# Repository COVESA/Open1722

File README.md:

<!-- PROJECT LOGO -->
<br />
<div align="center">

<h2 align="center">COVESA Open1722</h2>

  <p align="center">
    Open1722  is an implementation of the IEEE 1722 protocol, for streaming audio/video, tunneling CAN/LIN messages and enabling remote access to peripheral bus systems.
    <br />
    <br />
    <a href="https://github.com/COVESA/Open1722/issues">Report Bug</a>
    ·
    <a href="https://github.com/COVESA/Open1722/issues">Request Feature</a>
    </p>
</div>

### Maintainers

* [Naresh Nayak - University of Applied Sciences Furtwangen (HFU)](https://github.com/nayakned)
* [Adriaan Niess - Robert Bosch GmbH](https://github.com/adriaan-niess)
* [Sebastian Schildt - University of Applied Sciences Heilbronn (HHN)](https://github.com/SebastianSchildt)

## Introduction

Open1722 is a fork of [AVNU/libavtp](https://github.com/Avnu/libavtp) which is an open source reference implementation of the Audio Video Transport Protocol (AVTP) specified in IEEE 1722-2025 spec. _libavtp_ primarily focuses on audio video data formats of the IEEE 1722-2016 spec.

IEEE 1722 is also gaining a lot of traction in the automotive community, mainly, to bridge fieldbus technologies over automotive Ethernet. In particular the AVTP Control Formats (ACF) specify serialization for a set of data formats relevant for automotive applications (e.g., CAN, LIN, etc.). Open1722 extends/modifies _libavtp_ to also include these ACF formats.

Open1722 is under BSD License. For more information see LICENSE file.

## Implementation

This repository is organized as follows:
- The `src/` and `include/` folders contain the IEEE 1722 protocol implementation. We strive to make the implementation platform independant and avoid usage of platform specific headers or libraries. For now the implementation is tested only on Linux.
- The `examples/` folder contains various applications that use our Open1722 library. Most applications are targeted to Linux platforms. Few applications (e.g. [_acf-can-bridge_](./examples/acf-can/zephyr/)) are also ported for Zephyr RTOS. Compilation instructions for Zephyr is available in the corresponding folder of the application.

Before building Open1722 make sure you have installed the following software :
* CMake >= 3.20
* CMocka >= 1.1.0 (For running unit tests. This can be installed on Debian/Ubuntu using ```sudo apt install libcmocka-dev```)

Alternatively, you can use VS Code to run the provided dev container which takes care of the dependencies.

The first step to build Open1722 is to generate the Makefile and build the project.
```
$ mkdir build
$ cd build
$ cmake ..
$ make
```
This builds the libraries _libopen1722_ containing all the data formats specified in the IEEE 1722-2025 specification along with _libopen1722custom_ which contains customized serialization formats which can be sent over IEEE 1722.

To execute available unit tests:
```
$ cmake ..
$ make unittests
$ make test
```

The [examples](./examples/) can be built as follows:
```
$ make examples
```

The build can be cleaned using the following command:
```
$ make clean
```

To install Open1722 on your system run:
```
$ sudo make install
```

To cross-compile for aarch64 (e.g. Raspberry Pi), you can use the [toolchain file](./aarch64.toolchain) we provided. Note that this requires a fresh build process with a new ```build``` folder.
```
$ sudo apt install gcc-aarch64-linux-gnu libc6-dev-arm64-cross binutils-aarch64-linux-gnu
$ cmake .. -DCMAKE_TOOLCHAIN_FILE=../aarch64.toolchain
$ make
```

## AVTP Formats Support

AVTP protocol defines several AVTPDU type formats (see Table 7 from IEEE 1722-2025 spec).

The following is the list of the formats currently supported by Open1722:
 - AAF (PCM encapsulation only)
 - CRF
 - CVF (H.264, MJPEG, JPEG2000)
 - RVF
 - AVTP Control Formats (ACF) with Non-Time-Synchronous as well as Time-Synchronous formats (see Table 23 from IEEE 1722-2025 spec)
    - CAN (v1 & v2)
    - CAN Brief (v1 & v2)
    - CAN-XL
    - CAN-XL Brief
    - CRC
    - Flexray
    - LIN
    - MOST
    - GPC
    - Sensor
    - Sensor Brief
    - Generic Byte Bus
    - Abbreviated Byte Bus
    - Generic Image Sensor Format (GISF)
    - I2C
    - I2C Brief
  - Custom formats not included in the standard but can be transported on top of IEEE 1722
    - COVESA Vehicle Signal Specification (VSS) [(Protocol description)](./examples/acf-vss/protocol_description/acf-vss.md)

## Examples

The `examples/` directory provides sample applications which demonstrate the Open1722 functionalities. Each example directory contains a README file that includes specific details on its functionality, configuration, and dependencies.

To execute the IEEE 1722 CAN Talker application:
```
$ ./build/examples/acf-can/linux/acf-can-talker
```

### Programming Tutorial

Here's a small example how the Open1722 library can be used to build and parse IEEE 1722 Protocol Data Units (aka PDUs). First define a C struct for a custom IEEE 1722 packet that can be used to transport a CAN and a LIN message. The frame begins with a Time-synchronous Control Format (TSCF) header. Alternatively a Non-Timesynchronous Control Format (NTSCF) header could be used. After the TSCF header a list of AVTP Control Format (ACF) messages follows. The first ACF message is a ACF CAN message which consists of ACF CAN header as well as a payload section to carry an 8-byte CAN frame. Similarly to the CAN message, another ACF message for LIN is added.

When combining IEEE 1722 header/message structs directly in memory to form a packet, the resulting layout must not contain compiler-inserted padding bytes. Use a compiler hint to enforce packed layout (for example `__attribute__((packed))` with GCC/Clang).

``` C
// my_1722_pdu.h

#include "avtp/Udp.h"
#include "avtp/acf/Tscf.h"
#include "avtp/acf/Can.h"
#include "avtp/acf/Lin.h"

#define CAN_PAYLOAD_LEN 8
#define LIN_PAYLOAD_LEN 4

typedef struct __attribute__((packed)) {
    // IEEE 1722 UDP encapsulation header (optional)
    Avtp_Udp_t udp;
    // IEEE 1722 TSCF header (version 0 layout; use Avtp_TscfV1_t for version 1)
    Avtp_TscfV0_t tscf;
    // IEEE 1722 ACF message #1
    Avtp_Can_t can;
    uint8_t canPayload[CAN_PAYLOAD_LEN];
    // IEEE 1722 ACF message #2
    Avtp_Lin_t lin;
    uint8_t linPayload[LIN_PAYLOAD_LEN];
} My1722Pdu_t;
```

In the next step we're going to c

``` C
// talker.h

#include "my_1722_pdu.h"

int main()
{
    My1722Pdu_t pdu;

    // Init UDP encapsulation header
    Avtp_Udp_Init(&pdu.udp);

    // Init TSCF header. Use Avtp_Tscf_Init(&pdu.tscf, version) to pick the
    // version at runtime; version 0 and version 1 have different layouts and
    // header lengths (Avtp_TscfV0_t / Avtp_TscfV1_t).
    Avtp_Tscf_InitV0(&pdu.tscf);
    Avtp_CommonHeader_SetVersion((Avtp_CommonHeader_t *)&pdu.tscf, 0);
    Avtp_Tscf_SetSequenceNum(&pdu.tscf, 123);
    Avtp_Tscf_SetStreamId(&pdu.tscf, 0xAABBCCDDEEFF);
    Avtp_Tscf_SetTv(&pdu.tscf, true);
    Avtp_Tscf_SetAvtpTimestamp(&pdu.tscf, 0x11223344);

    // Init CAN ACF message
    Avtp_Can_Init(&pdu.can);
    Avtp_Can_SetCanBusId(&pdu.can, 4);
    uint8_t canFrame[CAN_PAYLOAD_LEN] = {0x11, 0x22, 0x33, 0x44, 0x55, 0x66, 0x77, 0x88};
    memcpy(pdu.can.payload, canFrame, CAN_PAYLOAD_LEN);

    // Init LIN ACF message
    Avtp_Lin_Init(&pdu.lin);
    uint8_t linFrame[LIN_PAYLOAD_LEN] = {0x11, 0x22, 0x33, 0x44};
    memcpy(pdu.lin.payload, linFrame, LIN_PAYLOAD_LEN);

    // Send packet to network using socket API ...
    uint8_t* data = &pdu;
    size_t dataLen = sizeof(My1722Pdu_t);
    // int socket = ...
    // sendto(socket, data, dataLen, 0);
}
```

## Open1722 API

To learn what you can expect from the Open1722 API and to get a starting point in case you want to extend Open1722 see the [API design documentation](docs/api-design.md).

## Alignment and Performance

PDUs may sit at any byte offset in a buffer: the accessors make no alignment assumptions, and on targets with hardware unaligned access the field-access engine still compiles to single-instruction reads and writes. See [alignment.md](docs/alignment.md) for the spec background, the generated-code details, and how to hint a guaranteed alignment on strict-alignment targets.

## Inline Functions and Shared Library Exports

Open1722 uses `static inline` functions for field accessors to enable compiler optimizations on embedded targets. These same functions are also exported as regular symbols in the shared library for FFI users. See [inline.md](docs/inline.md) for details.

## Rust
Open1722 is consciously implemented in C and designed to effciently run on anything with a processor. Now we _do_ know Rust is awesome and has many advantages for some use cases. If you happen to be one of those guys: There is probably no need to wrap Open1722 yourself or endavour in yet another "let's rewrite it in Rust" initiative. Instead, check out this nice third-party wrapper to Open1722 first: https://crates.io/crates/open1722/

## Contribute to Open1722

For detailed information see our [contribution guide](./CONTRIBUTING.md)!

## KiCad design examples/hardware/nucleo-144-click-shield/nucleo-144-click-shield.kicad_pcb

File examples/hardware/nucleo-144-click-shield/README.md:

# NUCLEO-144 Click Shield

This directory contains the KiCad project for the NUCLEO-144 Click Shield, a hardware add-on board designed to attach mikroBus click boards to an STM32 NUCLEO-144 development board. This clicks shield is useful to run various Open1722 examples for Zephyr on a modular platform.

## Use

Open the `.kicad_pro` file in KiCad to work with the project. From there you can edit the schematic, update the PCB layout, and regenerate fabrication outputs.

If you need a stable reference for the released design, use the files in `v1.1/`.

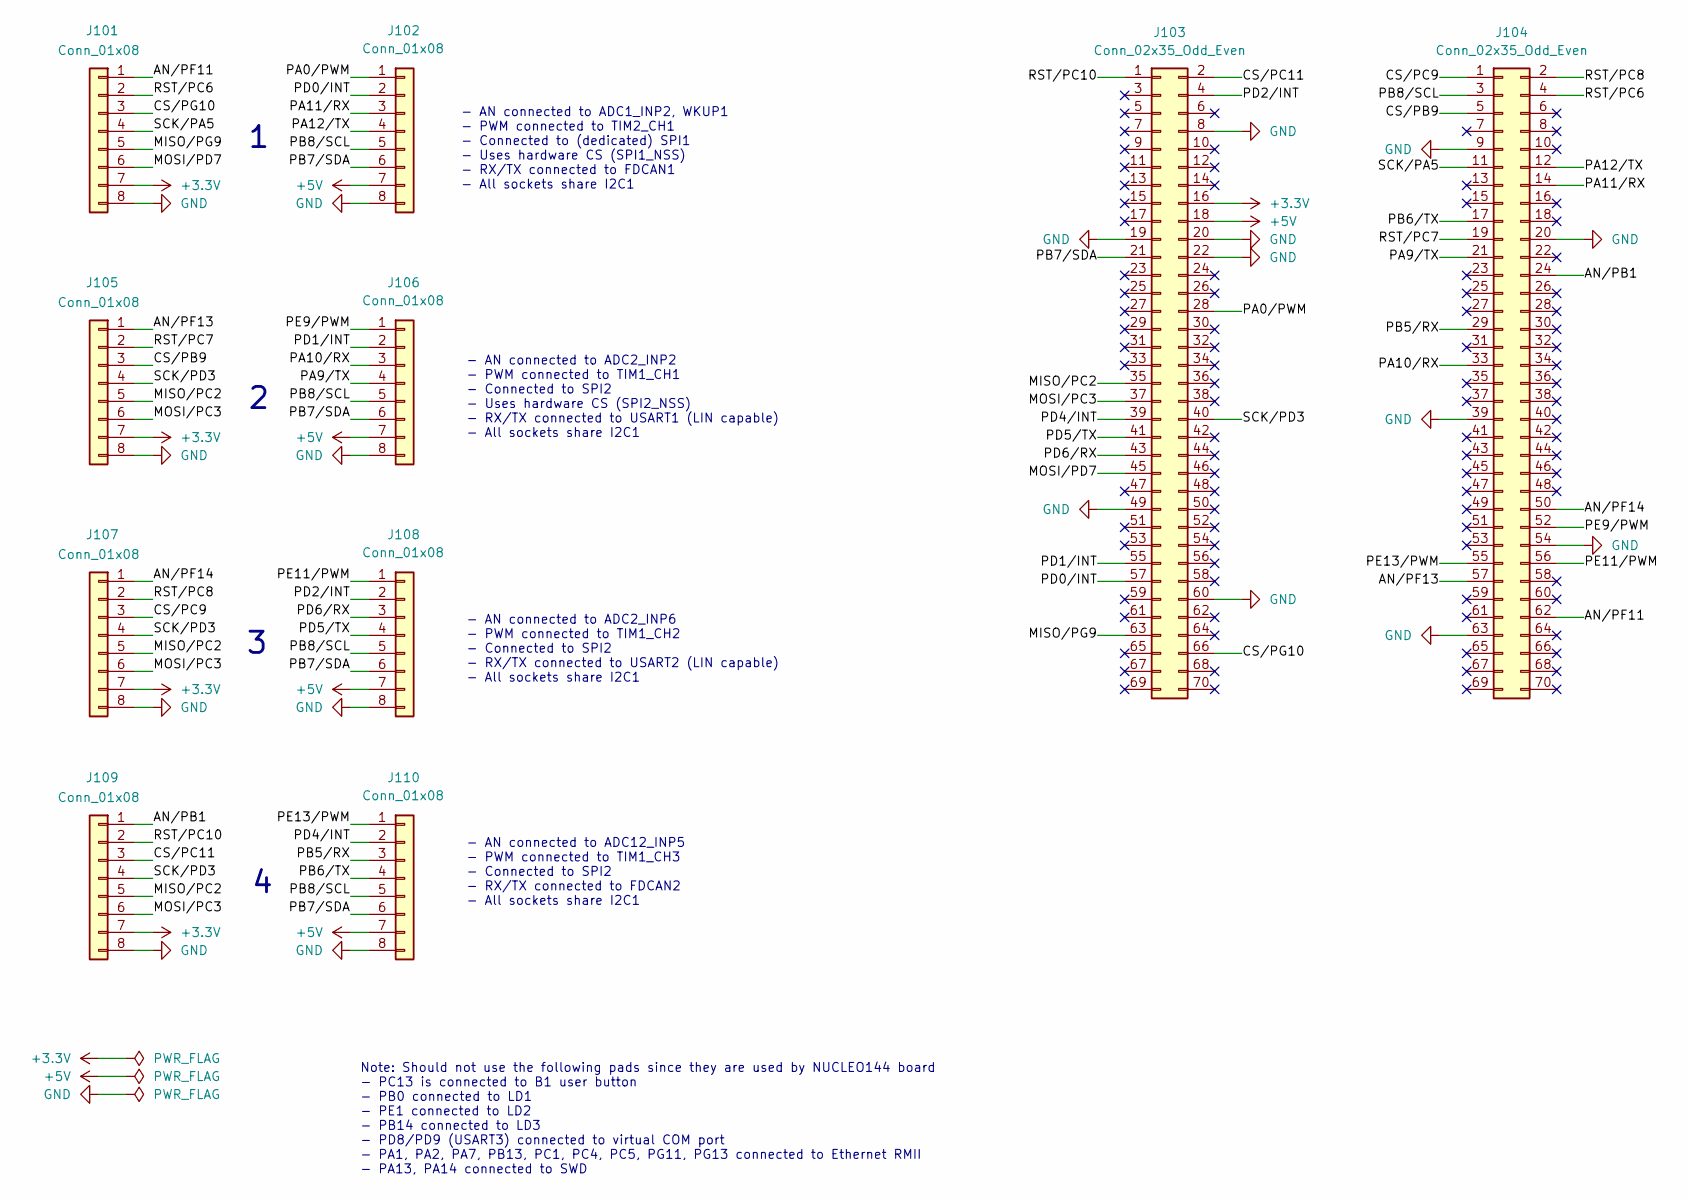
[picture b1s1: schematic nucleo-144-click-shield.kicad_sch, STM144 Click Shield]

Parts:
J101, J102, J105, J106, J107, J108, J109, J110: Conn_01x08; PinSocket_1x08_P2.54mm_Vertical
J103, J104: Conn_02x35_Odd_Even; PinSocket_2x36_P2.54mm_Vertical

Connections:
+3.3V: J101.7, J103.16, J105.7, J107.7, J109.7
+5V: J102.7, J103.18, J106.7, J108.7, J110.7
/AN/PB1: J104.24, J109.1
/AN/PF11: J101.1, J104.62
/AN/PF13: J104.57, J105.1
/AN/PF14: J104.50, J107.1
/CS/PB9: J104.5, J105.3
/CS/PC9: J104.1, J107.3
/CS/PC11: J103.2, J109.3
/CS/PG10: J101.3, J103.66
/MISO/PC2: J103.35, J105.5, J107.5, J109.5
/MISO/PG9: J101.5, J103.63
/MOSI/PC3: J103.37, J105.6, J107.6, J109.6
/MOSI/PD7: J101.6, J103.45
/PA0/PWM: J102.1, J103.28
/PA9/TX: J104.21, J106.4
/PA10/RX: J104.33, J106.3
/PA11/RX: J102.3, J104.14
/PA12/TX: J102.4, J104.12
/PB5/RX: J104.29, J110.3
/PB6/TX: J104.17, J110.4
/PB7/SDA: J102.6, J103.21, J106.6, J108.6, J110.6
/PB8/SCL: J102.5, J104.3, J106.5, J108.5, J110.5
/PD0/INT: J102.2, J103.57
/PD1/INT: J103.55, J106.2
/PD2/INT: J103.4, J108.2
/PD4/INT: J103.39, J110.2
/PD5/TX: J103.41, J108.4
/PD6/RX: J103.43, J108.3
/PE9/PWM: J104.52, J106.1
/PE11/PWM: J104.56, J108.1
/PE13/PWM: J104.55, J110.1
/RST/PC6: J101.2, J104.4
/RST/PC7: J104.19, J105.2
/RST/PC8: J104.2, J107.2
/RST/PC10: J103.1, J109.2
/SCK/PA5: J101.4, J104.11
/SCK/PD3: J103.40, J105.4, J107.4, J109.4
GND: J101.8, J102.8, J103.8, J103.19, J103.20, J103.22, J103.49, J103.60, J104.9, J104.20, J104.39, J104.54, J104.63, J105.8, J106.8, J107.8, J108.8, J109.8, J110.8

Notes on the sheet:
- AN connected to ADC12_INP5 - PWM connected to TIM1_CH3 - Connected to SPI2 - RX/TX connected to FDCAN2 - All sockets share I2C1
Note: Should not use the following pads since they are used by NUCLEO144 board - PC13 is connected to B1 user button - PB0 connected to LD1 - PE1 connected to LD2 - PB14 connected to LD3 - PD8/PD9 (USART3) connected to virtual COM port - PA1, PA2, PA7, PB13, PC1, PC4, PC5, PG11, PG13 connected to E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
- AN connected to ADC2_INP6 - PWM connected to TIM1_CH2 - Connected to SPI2 - RX/TX connected to USART2 (LIN capable) - All sockets share I2C1
- AN connected to ADC1_INP2, WKUP1 - PWM connected to TIM2_CH1 - Connected to (dedicated) SPI1 - Uses hardware CS (SPI1_NSS) - RX/TX connected to FDCAN1 - All sockets share I2C1
- AN connected to ADC2_INP2 - PWM connected to TIM1_CH1 - Connected to SPI2 - Uses hardware CS (SPI2_NSS) - RX/TX connected to USART1 (LIN capable) - All sockets share I2C1

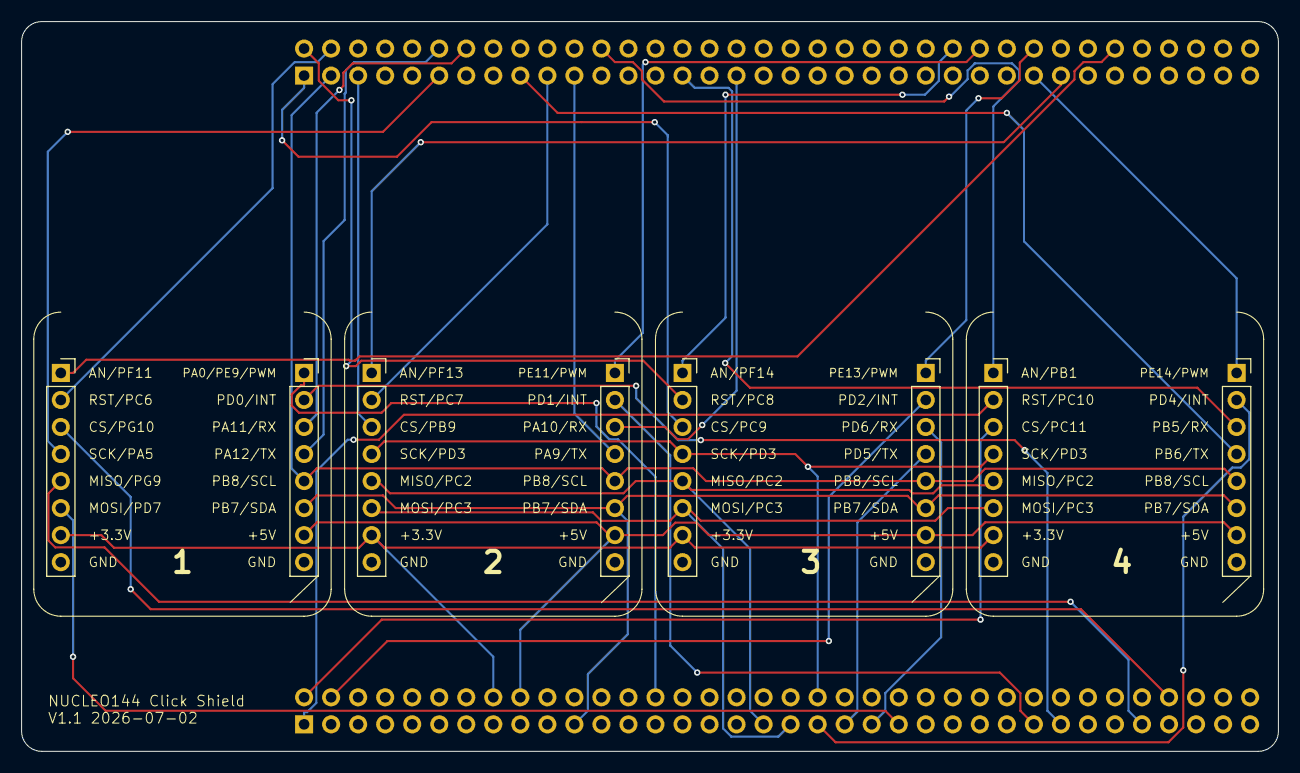
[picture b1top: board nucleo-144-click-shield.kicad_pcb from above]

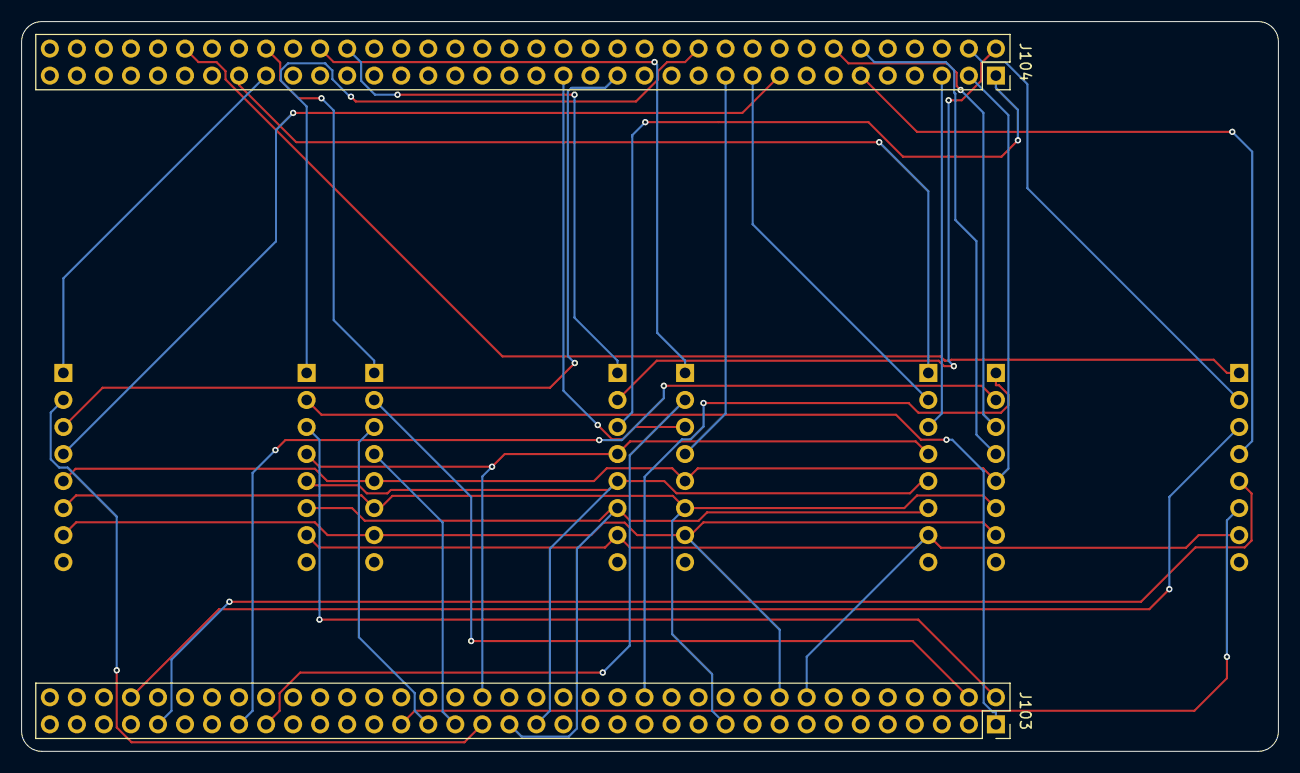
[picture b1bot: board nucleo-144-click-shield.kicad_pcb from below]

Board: 4 copper layers, 118.1 x 68.6 mm, 10 parts (2 on the bottom side), 39 nets.

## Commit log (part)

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2025-08-15 Fix compiler warnings
2025-08-15 Adds Avtp_<Format>_IsValid() functions to all AVTP/ACF frame formats
2025-08-15 Added linking to zephyr_interface to fix compilation fot native_sim.
2025-08-15 Fixed the print messages while starting acf-can applications.
2025-08-15 Add SPDX identifier check to GHA
2025-08-15 Allow installation of examples if they are built.
2025-08-15 First version of acf-can-bridge compiled for portenta h7 using Zephyr.
2025-08-15 Updated APIs for setting 1-bit fields for all formats.
2025-08-15 Fixed minor bugs due to unsigned values and continue statements.
2025-08-15 A kernel module wrapper fro ACF-CAN
    This is a Linux kernel driver that provides a
    virtual CAN interface for sending IEEE-1722
    ACF-CAN frames directly.
2025-08-15 Fixed typos in the API changes for 1-bit setter functions.
2025-08-15 Moved linux specific CAN examples into linux/ folder.
2025-08-15 Changes to get acf-can-bridge working on Arduino Portenta H7.
2025-08-15 Update license information for kernel module
2025-08-15 Allow dual license in SPDX checker
2025-08-15 Added a README.md file on how to compile acf-can-bridge for Zephyr.
2025-08-15 fixed typo in one header in README
2025-08-15 consistent arg-parse with other examples
2025-08-15 Refactored coomon code for ACF-CAN Listener to acf-can-common.c
2025-08-15 Fixed seg faults in CAN apps due to missing break.
2025-08-15 Added error messages when starting/binding to CAN socket runs into an error.
2025-08-15 Make API compatible with C++
2025-08-15 Removed stdint.h inclusion. Using the inclusion from avtp/Defines.h
2025-08-15 CMake files updated to support build for QNX
2025-08-15 Add Contributing guidelines
2025-08-15 update talker to new Get/Set API
2025-08-15 Made changes to CANBrief API for consistency with CAN API.
2025-08-15 Adjusting thread priorities to prevent buffer overflows in Arsuino Portenta H7.
2025-08-15 Added first version of an acf-can-bridge.
2025-08-15 Refactored cmake build process for selective building process.
2025-08-15 Added crosscompile toolchain file for aarch64.
2025-08-15 Fix copy/paste errors in CanBrief field accessors
2025-08-15 Fixed the parsing of received AVTP frames to account for Ethernet padding.
2025-08-15 Extended GHA for Arduino Portenta H7.
2025-08-15 First version of acf-can-bridge application compiled for Zephyr.
2025-08-15 Updated documentation for the acf-can-bridge.
2025-08-15 CAN and FlexRay checks
2025-08-15 Change the can_send() from blocking to non-blocking execution.
2025-08-15 First version of getting Zephyr app compiled in open1722 source tree.
2025-08-15 Updated CMake Variables for easy integration in other CMake Projects.
2025-08-15 Added compiler flags for warnings in libopen1722.
2025-08-15 Replaces the return type of avtp_<Format>_valid method from boolean to uint8_t. Adds a definition for TRUE and FALSE in Defines.h
2025-08-15 Added talker and listener stream ids as command line parameters.
2025-08-15 Github action to test build of kernel module
2025-08-15 Updated Avtp_CanBrief_GetPayload and Avtp_Can_GetPayload for constant pointer to a constant
2025-08-15 Replaced printf statements in acf-can appl. with LOG.
2025-08-15 Updated SPDX-License-Identifier to fix SPDX check
2025-08-15 eBPF benchmarking tool
2025-08-15 Updated Avtp_CanBrief_GetPayload for constant pointer to a constant
2025-08-15 Fix SPDX identifier for crf-talker
2025-08-15 Updated CMakeLists.txt alignment.
2025-08-15 Dockerfile for acfcanbridge and general MUSL compile fixes
2025-08-15 Updated getters constant pointer to a constant
2025-08-15 Include stddef.h for size_t
2025-08-21 Update README.md
    Per a Technical Steering Team vote on 8/18/2025, Open1722 has reached the Mature Project Status. So, it no longer needs the Incubating Status badge. Hence, it was removed.
2025-09-01 Fancy eBPF commit
2025-11-10 Initial plan
2025-11-10 Add unit tests for FlexRay, LIN, MOST, GPC, and Sensor ACF formats
2025-11-10 Add unit tests for UDP encapsulation and CommonHeader
2025-11-10 Final test coverage improvement summary
2025-11-10 Update .gitignore to exclude CodeQL build directory
2026-02-16 Test for failing badge
2026-02-16 Fixed failing tests for the badge.
2026-02-16 Inlined all getters/setters of the ACF CAN format.
2026-02-16 Inlined getters/setters for ACF CAN Brief format.
2026-02-16 Inlined all functions of AcfCommon module.
2026-02-16 Inlined functions in ACF GPC and ACF FlexRay.
2026-02-16 Fixed compilation errors due to removal for SetField/GetField functions.
2026-02-16 Removed duplicate includes.
2026-02-16 Inlined all getters/setters for ACF types and subtypes.
2026-02-19 Moved unit tests to CXX files to test C++ bindings implicitly.
2026-02-19 Fixed SPDX license headers for unit test files.
2026-02-19 Unit test run with C as well as C++ compiler to check for compilation.
2026-02-20 Replaced duplicate CPP target creation using a function.
2026-04-13 Support new .newlink signature in Linux kernel>=6.10
2026-04-15 Added relevant POSIX headers for networking.
    Due to a change in Zephyr structure, we need to now specifically add headers for POSIX utilities.
    See https://github.com/zephyrproject-rtos/zephyr/commit/ac859d0e7736bbffafeb4c1f0faab6b5a60a8922 for the corresponding Zephyr commit.
2026-04-15 Updated GHA to use latest checkout actions (v5).
2026-04-18 Add scheduled cron jobs to build workflows for consistency
2026-04-18 Add ACF_ABB and ACF_GBB formats
2026-04-19 Update list of maintainers
2026-04-19 Update ACF types
2026-04-19 Update GBB/ABB ACF formats
2026-04-19 Add ACF_GISF format
2026-04-23 Improve ACF_ABB, ACF_GBB, ACF_GISF formats
2026-04-23 Update ACF_ABB, ACF_GBB, ACF_GBB formats and add tests for GISF
2026-04-23 Add first tests for ACF_ABB format
2026-04-24 Add more tests to ACF_ABB and refactore ACF_GISF, ACF_ABB
2026-04-24 Add unit test for ACF_GBB format
2026-04-24 Update enum with ACF types
2026-04-24 Improve const correctness
2026-04-24 Remove gisf_data_length field from ACF_GISF type since this field was removed in final 1722-2025 spec
2026-04-24 Correctly use 2026 copyright notice
2026-04-24 Fix README formatting and enhance Zephyr application instructions
2026-04-24 Updated findings for running CAN examples on native_sim on Zephyr
2026-04-24 Fixed minor typos in README.md for Zephyr build.
2026-04-24 Removed the incubation notice from README.md.
2026-04-26 Removed $ symbols from the bash command snippets.
2026-04-26 Added zephyr_generated_headers as build dependency.
    This is as per the suggestion in https://github.com/zephyrproject-rtos/zephyr/blob/e2a556ff64170573f21a7e4d21fcb6286f5fb8eb/doc/releases/migration-guide-4.4.rst#kernel to migrate to version 4.4 Kerne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
2026-04-27 Add CAN-XL AVTP control format
2026-04-27 Add CAN-XL-Brief AVTP control format
2026-04-27 Add CAN-XL ACF formats and unit tests
2026-04-27 Fix references
2026-04-28 Improve docstrings
2026-04-28 Add ACF_CAN_V2 and ACF_CAN_BRIEF_V2 formats
2026-05-05 acf/vss: fix unbounded reads in string-array (de)serialisation
    Avtp_Vss_DeserializeStringArray and Avtp_Vss_GetVSSDataStringArrayLength
    in src/avtp/acf/custom/Vss.c walk an on-wire string-array layout of
    [length-prefix : 2 bytes][string : length bytes] pairs. Both had
    serious bounds-check defects allowing crafted network input to drive
    out-of-bounds reads:
    1. Avtp_Vss_DeserializeStringArray declared `uint16_t idx = 0;` and
2026-05-07 Updated README.md to reflect the addition of formats from IEEE 1722-2025
    - Changed the version of IEEE 1722 from 2016 to 2025
    - Added formats to the list of supported formats: CAN v2, CAN-XL,
    ABB, GBB, GISF and their brief versions
2026-05-07 Bump golang.org/x/image in /examples/acf-can/ebpf-benchmarking-extensive
    Bumps [golang.org/x/image](https://github.com/golang/image) from 0.18.0 to 0.38.0.
    - [Commits](https://github.com/golang/image/compare/v0.18.0...v0.38.0)
    ---
    updated-dependencies:
    - dependency-name: golang.org/x/image
    dependency-version: 0.38.0
2026-05-07 acf/can: reject invalid CAN payload lengths instead of silent truncation
    Avtp_Can_GetCanPayloadLength and Avtp_CanBrief_GetCanPayloadLength
    silently produced wrong values when a PDU encoded an AcfMsgLength
    field larger than ~63 quadlets:
    uint8_t acf_msg_length = Avtp_Can_GetAcfMsgLength(pdu) * 4;
    return acf_msg_length - AVTP_CAN_HEADER_LEN - pad;
    The (uint8_t) variable holding the byte-count truncated mod 256, so
2026-05-07 acf/can: address review feedback — centralise validity in IsValid
    Per the discussion in #128 with @nayakned, @adriaan-niess, and
    @SebastianSchildt, restructure the fix to:
    1. Keep Avtp_Can_GetCanPayloadLength / Avtp_CanBrief_GetCanPayloadLength
    lean. Compute in uint16_t internally to avoid the original
    silent-truncation hazard, narrow back to uint8_t for the return.
    Document the precondition that callers must invoke IsValid first.
2026-05-07 test: replace bogus 'Init-only is valid' fixture with proper frames
    The IsValid extension agreed in the review thread (classic CAN <= 8
    bytes, CAN-FD <= 64 bytes, plus the underflow guard
    msg_length_bytes >= header + pad) caused the existing first assertion
    in can_is_valid to fail: a freshly Avtp_Can_Init'd PDU has
    AcfMsgLength == 0, which describes a frame shorter than its own
    header and so is now correctly rejected as malformed.
2026-05-07 test: add malformed-input case for VSS string-array parser
    Per @SebastianSchildt's review on this PR. Constructs a 23-byte
    on-wire fixture identical to the well-formed vss_data_string_array
    test, except the third length prefix is patched from 0x0007 to
    0x00AA — so the third entry claims 170 bytes of body but only 7
    bytes of buffer remain after its length prefix.
    Asserts:
2026-05-11 Clean up AI comments
2026-05-11 docs: clarify packed layout requirement in README tutorial
    Agent-Logs-Url: https://github.com/COVESA/Open1722/sessions/98dfb8ff-896a-4229-821a-434868ee0007
2026-05-12 docs: adjust README CAN and LIN payload sizes
    Agent-Logs-Url: https://github.com/COVESA/Open1722/sessions/59c361f8-8dca-42c0-999b-ca2e9efc2988
2026-05-12 docs: polish README tutorial wording
    Agent-Logs-Url: https://github.com/COVESA/Open1722/sessions/59c361f8-8dca-42c0-999b-ca2e9efc2988
2026-05-13 First agentic version of removing conversion and sign-conversion warnings.
    - Set Wconversion and Wsign-conversion in cmake scripts.
    - Explicit casting for getter functions of different formats.
2026-05-13 First version of agentic changes for removing conversion & sign-conversion warnings.
    - Added -Wconversion and -Wsign-conversion to cmake build options
    - Explicit casts for getter functions for all data formats.
2026-05-22 feat(examples): add ACF-LIN talker/listener example (#21)
    Add a pair of example applications demonstrating use of the ACF-LIN
    PDU (IEEE Std. 1722-2016, chapter 9.4.5):
    - acf-lin-talker: sends a simulated LIN frame once per second over
    Ethernet (raw TSN) or UDP, carrying a single-byte incrementing
    counter as payload. Supports NTSCF and TSCF control formats.
    - acf-lin-listener: receives ACF-LIN packets and prints the LIN bus
2026-05-22 ci: add .clang-format and PR format-check step (#30)
    Add a .clang-format configuration that captures the existing Open1722
    code style:
    - 4-space indent, no tabs
    - Linux brace style (function braces on a new line, control-structure
    braces on the same line as the keyword)
    - case labels at switch indent level (IndentCaseLabels: false)
